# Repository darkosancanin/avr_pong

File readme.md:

### Overview 
ATmega328 based implementation of the classic game PONG with hardware design. The implementation of the game is a one player game with the ability to choose the skill level for the computer AI. The user paddle input control in hardware is done via a potentiometer with the TV and audio signal being output via a RCA connector and the video encoded using the PAL standard.

### PAL Signal Overview
- The PAL TV signal in the game is generated completely by the TVOut Arduino library (https://code.google.com/p/arduino-tvout/). The overview below is purely for the sake of learning.
- PAL (Phase Alternating Line) requires 625 scanlines to create one image on the screen.
- Not all 625 lines can be seen, some are used for sync pulses (and later for teletext etc), ~576 lines are visible.
- The picture is drawn one half at a time (thus the Alternating part in the name), all even lines are drawn first, then the next cycle will display all odd lines and so on. 
- Voltage levels are used to determine shades of between white and black it will render, black = 0.3V and white = 1V. (Color signal is generated differently, not covered here.)
- A voltage ladder is created by using a 470 Ohm and a 1K Ohm resistor to generate the two required voltage levels.
- Each scan line takes 64us (microseconds) to render. 12us sync signals, then 52us for the image signals.
- The vertical frequency is 50Hz, so the screen is updated with 50 half images per second, which is 25 full images per second. 
- See more at http://en.wikipedia.org/wiki/PAL

### Implementation Overview
- The game implementation is based on the code for the Pong game that is part of the Video Game Shield from Wayne and Layne (http://www.wayneandlayne.com/projects/video-game-shield/).
- I made it a one player game with very basic AI for the computer and added 3 skill levels to choose from.
- Other added features include: ability to pause, 'you won' or 'you lost' screens along with self promoting introduction screens.
- The user paddle changes sizes based on the skill level chosen.
- The ball direction when hit is based on where the ball hits the paddle, hitting the ball on the middle of the paddle will send it back in a straight line but hitting the far edges of the paddle will send the ball back at a much sharper angle.
- For the computer AI, the computer paddle moves one pixel closer in the direction of the ball every loop cycle but based on the skill level chosen it has a variable delay in reaction (it doesn't start moving until the ball is x pixels away from it). Another variable between skill levels is the 'loss of concentration' of the computer, basically the computer will not move its paddle every x amount of horizontal pixels that the ball moves across (implemented via the computer_loss_of_concentration_modulo_value variable).
- The TV signal generated is PAL and is purely implemented via TVOut Arduino library (https://code.google.com/p/arduino-tvout/). The resolution used is 120 x 96 pixels.
- The user paddle position is controlled by a analog to digital conversion reading from a 10K Ohm potentiometer.

### Schematic

### Breadboard

### TV

### PCB Layout

### Final Product

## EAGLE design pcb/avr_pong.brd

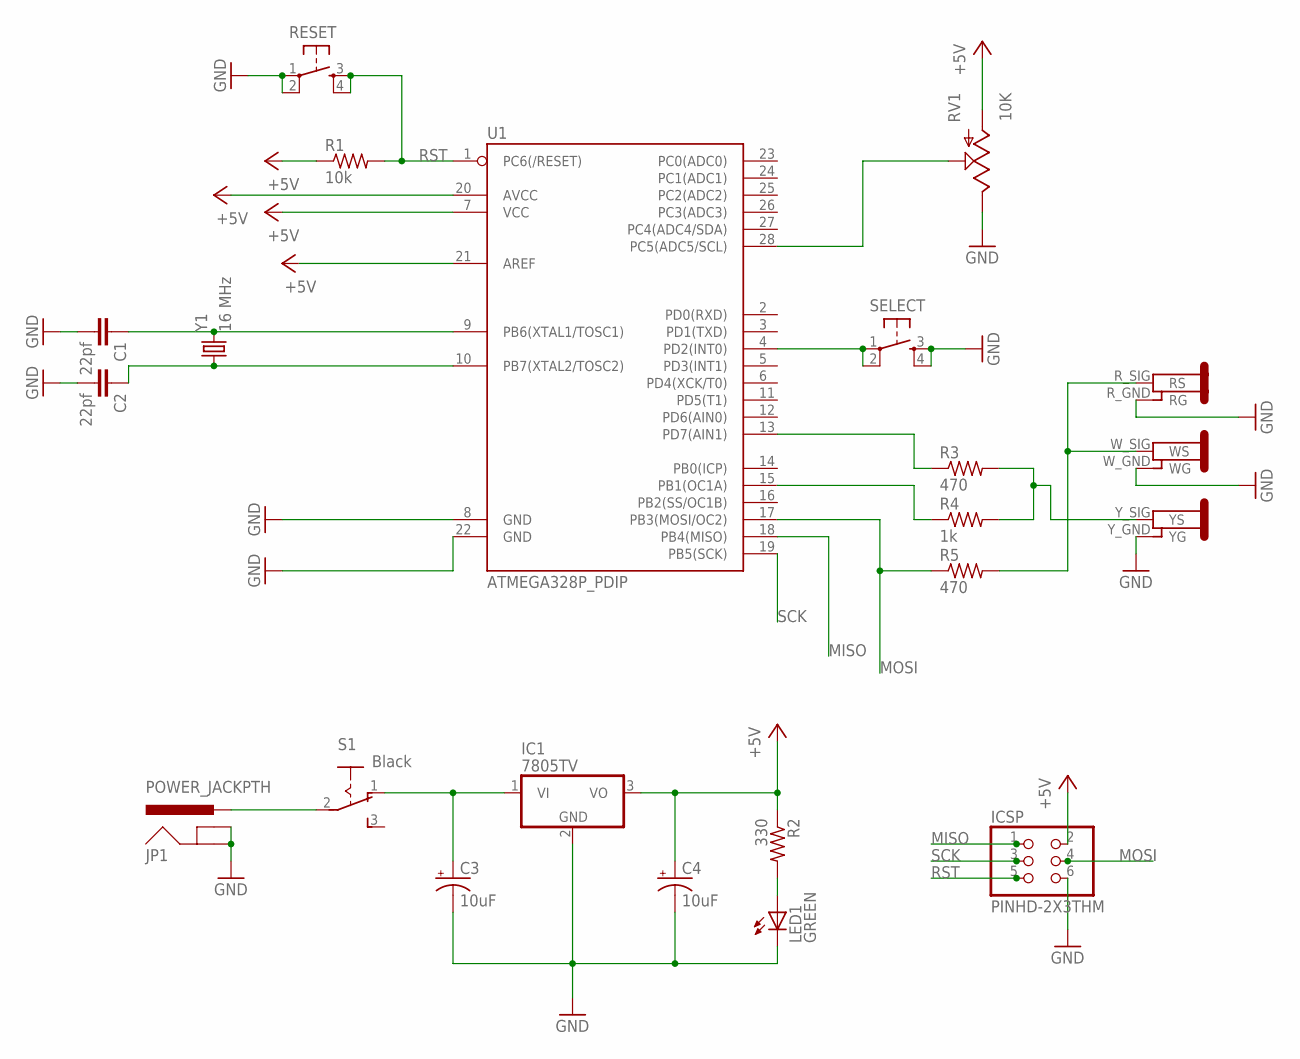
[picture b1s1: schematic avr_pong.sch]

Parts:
C1, C2: 22pf; CAP-PTH-SMALL-KIT
C3, C4: 10uF; E2,5-5
IC1: 7805TV; TO220V
ICSP: PINHD-2X3THM; ISP6
JP1: POWER_JACKPTH; POWER_JACK_PTH
LED1: GREEN; LED5MM
R1: 10k; 0207/10
R2: 330; 0207/10
R3, R5: 470; 0207/10
R4: 1k; 0207/10
RESET: TACTILE-SWITCH-PTH; TAC-SWITCH-PTH
RV1: 10K; POT_ALPHA_RV16AF-20
S1: Black; M251
SELECT: TACTILE-SWITCH-PTH; TAC-SWITCH-PTH
U1: ATMEGA328P_PDIP; DIL28-3
U$1: 3-RCA-JACK
Y1: 16 MHz; HC49US

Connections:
+5V: C4.+, IC1.3 (VO), ICSP.2, R1.1, R2.1, RV1.1 (A), U1.7 (VCC), U1.20 (AVCC), U1.21 (AREF)
GND: C1.2, C2.2, C3.-, C4.-, IC1.2 (GND), ICSP.6, JP1.GND, JP1.GNDBREAK, LED1.K (C), RESET.1, RESET.2, RV1.3 (E), SELECT.3, SELECT.4, U1.8 (GND), U1.22 (GND), U$1.R_GND (RG), U$1.W_GND (WG), U$1.Y_GND (YG)
MISO: ICSP.1, U1.18 (PB4(MISO))
MOSI: ICSP.4, R5.1, U1.17 (PB3(MOSI/OC2))
unnamed: C1.1, U1.9 (PB6(XTAL1/TOSC1)), Y1.2
unnamed: C2.1, U1.10 (PB7(XTAL2/TOSC2)), Y1.1
unnamed: R5.2, U$1.R_SIG (RS), U$1.W_SIG (WS)
unnamed: LED1.A, R2.2
unnamed: C3.+, IC1.1 (VI), S1.1 (O)
unnamed: JP1.PWR, S1.2
unnamed: RV1.2 (S), U1.28 (PC5(ADC5/SCL))
unnamed: SELECT.1, SELECT.2, U1.4 (PD2(INT0))
unnamed: R3.1, U1.13 (PD7(AIN1))
unnamed: R4.1, U1.15 (PB1(OC1A))
unnamed: R3.2, R4.2, U$1.Y_SIG (YS)
RST: ICSP.5, R1.2, RESET.3, RESET.4, U1.1 (PC6(/RESET))
SCK: ICSP.3, U1.19 (PB5(SCK))

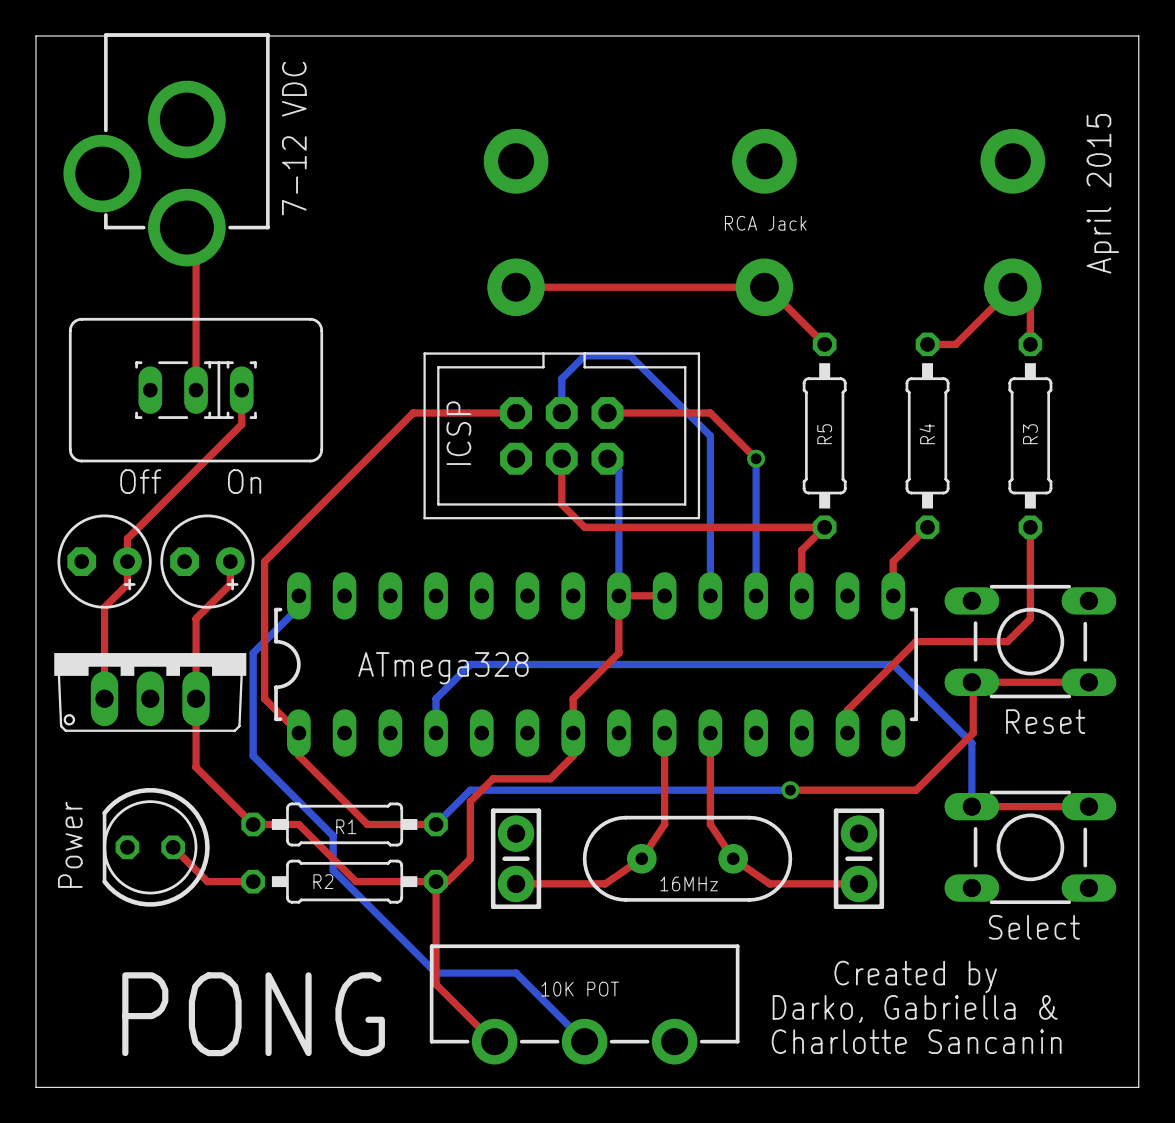
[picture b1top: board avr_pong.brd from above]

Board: 2 copper layers, 61.3 x 58.4 mm, 20 parts (0 on the bottom side), 17 nets.

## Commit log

2015-03-27 Initial commit.
2015-03-27 Added you won and game over screens.
2015-03-28 Added skill level menu.
2015-03-29 Added more realistic angles on ball hits.
2015-03-29 Customized skill level of computer at each level.
2015-03-30 Select button implementation.
2015-03-30 Minor bug fixes.
2015-03-30 Minor updates.
2015-03-30 Added start of schematic.
2015-03-30 Added datasheet.
2015-04-02 Added sleep mode.
2015-04-02 Removed debugging code.
2015-04-04 Skill selection correction.
2015-04-04 Removed sleep code as it will be powered by a DC jack and regulator.
2015-04-04 Added skip per introduction screen.
2015-04-04 Refactored wait code.
2015-04-04 Removed expert mode.
2015-04-06 Updated schematic.
2015-04-14 Moved pot to ADC5
2015-04-14 Updated schematic and added board layout.
2015-04-14 Updated board layout.
2015-04-15 Added PCB layout.
2015-05-12 Moved datasheets to own folder.
2015-05-12 Added libraries and readme file.
2015-05-12 Updated readme to fix link.
2015-05-12 Updated to included additional intro screen.
2015-05-17 Added eagle libraries.
2015-05-17 Added more images.
2015-05-17 Renamed file to lower case.
2015-05-17 Updated read me with images.
2015-05-17 Fixed readme image paths.
2015-06-11 Updated readme file.

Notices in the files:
parts and their libraries:
SparkFun-Capacitors: Licensing: Creative Commons ShareAlike 4.0 International - https://creativecommons.org/licenses/by-sa/4.0
